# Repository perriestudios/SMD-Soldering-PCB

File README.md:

# EE201 - Computer Hardware Skills

## SMD Soldering Practice Board

This PCB was designed with the goal of teaching students how to solder surface mount components. 

### Logic
The core logic of the circuit is the logic gates NOT, AND, OR and XOR. There is a multiplexer the outputs of one of these gates to the LED used for indication.

### Inputs
Power supply for the PCB is through a Type-C USB.

There are two tactile switches (push buttons), used to emulate the inputs A and B for the logic gates. The circuit is in active-high configuration with a weak pull-down resistor of 1k. This value was chosen to consolidate the BOM and limit the number of unique resistors(since LEDs also need current limiting resistors).

A DIP Switch is used to set the MUX configuration of Enable, S0 and S1. The other two inputs of the DIP switch can be used as a back up for inputs A and B.

### More SMT Packages Section

This section is used to provide an overview of some commonly available SMD packages of Passives, Transistors and ICs. Students will not solder this, it is just to give them a feel of how big components are.

### Packages that Students will be Soldering

- Resistors: 0805 and 1206
- LED: 1206
- Logic Gates: SOT323
- MUX: SOIC16
- Capacitor - 0603
- Tactile Switches - 6mmx6mm
- DIP Switch - 2.54mm pitch

### Design Choices

In the process of completing this design, there were several tradeoffs and decisions made. The biggest factor influencing the choices was a circuit of reasonable complexity for Sophomores to solder in approximately 1 hour.

- Logic gates were chosen as the design as it would be intuitive and fun. Some of the other ideas considered were a Digital Dice, Digital Modulator(PPM, PWM, PAM), a device that would indicate a threshold (temperature, etc).
- Limited the number of components to 15
- Limited the package size to 0805

### Possible improvements

- Wanted to interface an RGB Led, but didn't proceed considering cost and complexity of soldering.
- Find a way to control the routing of inputs of the logic gates. Currently there is only routing over the outputs. The logic gates will be draining power unnecessarily.
- Instead of using an off the shelf IC, one of the gates could be replaced with an actual TTL implementation. NOT gate would be the easiest.

### Acknowledgement

This design was inspired by [Educational Logic Gates PCB](https://www.pcbway.com/project/shareproject/Educational_logic_gates_PCB.html)

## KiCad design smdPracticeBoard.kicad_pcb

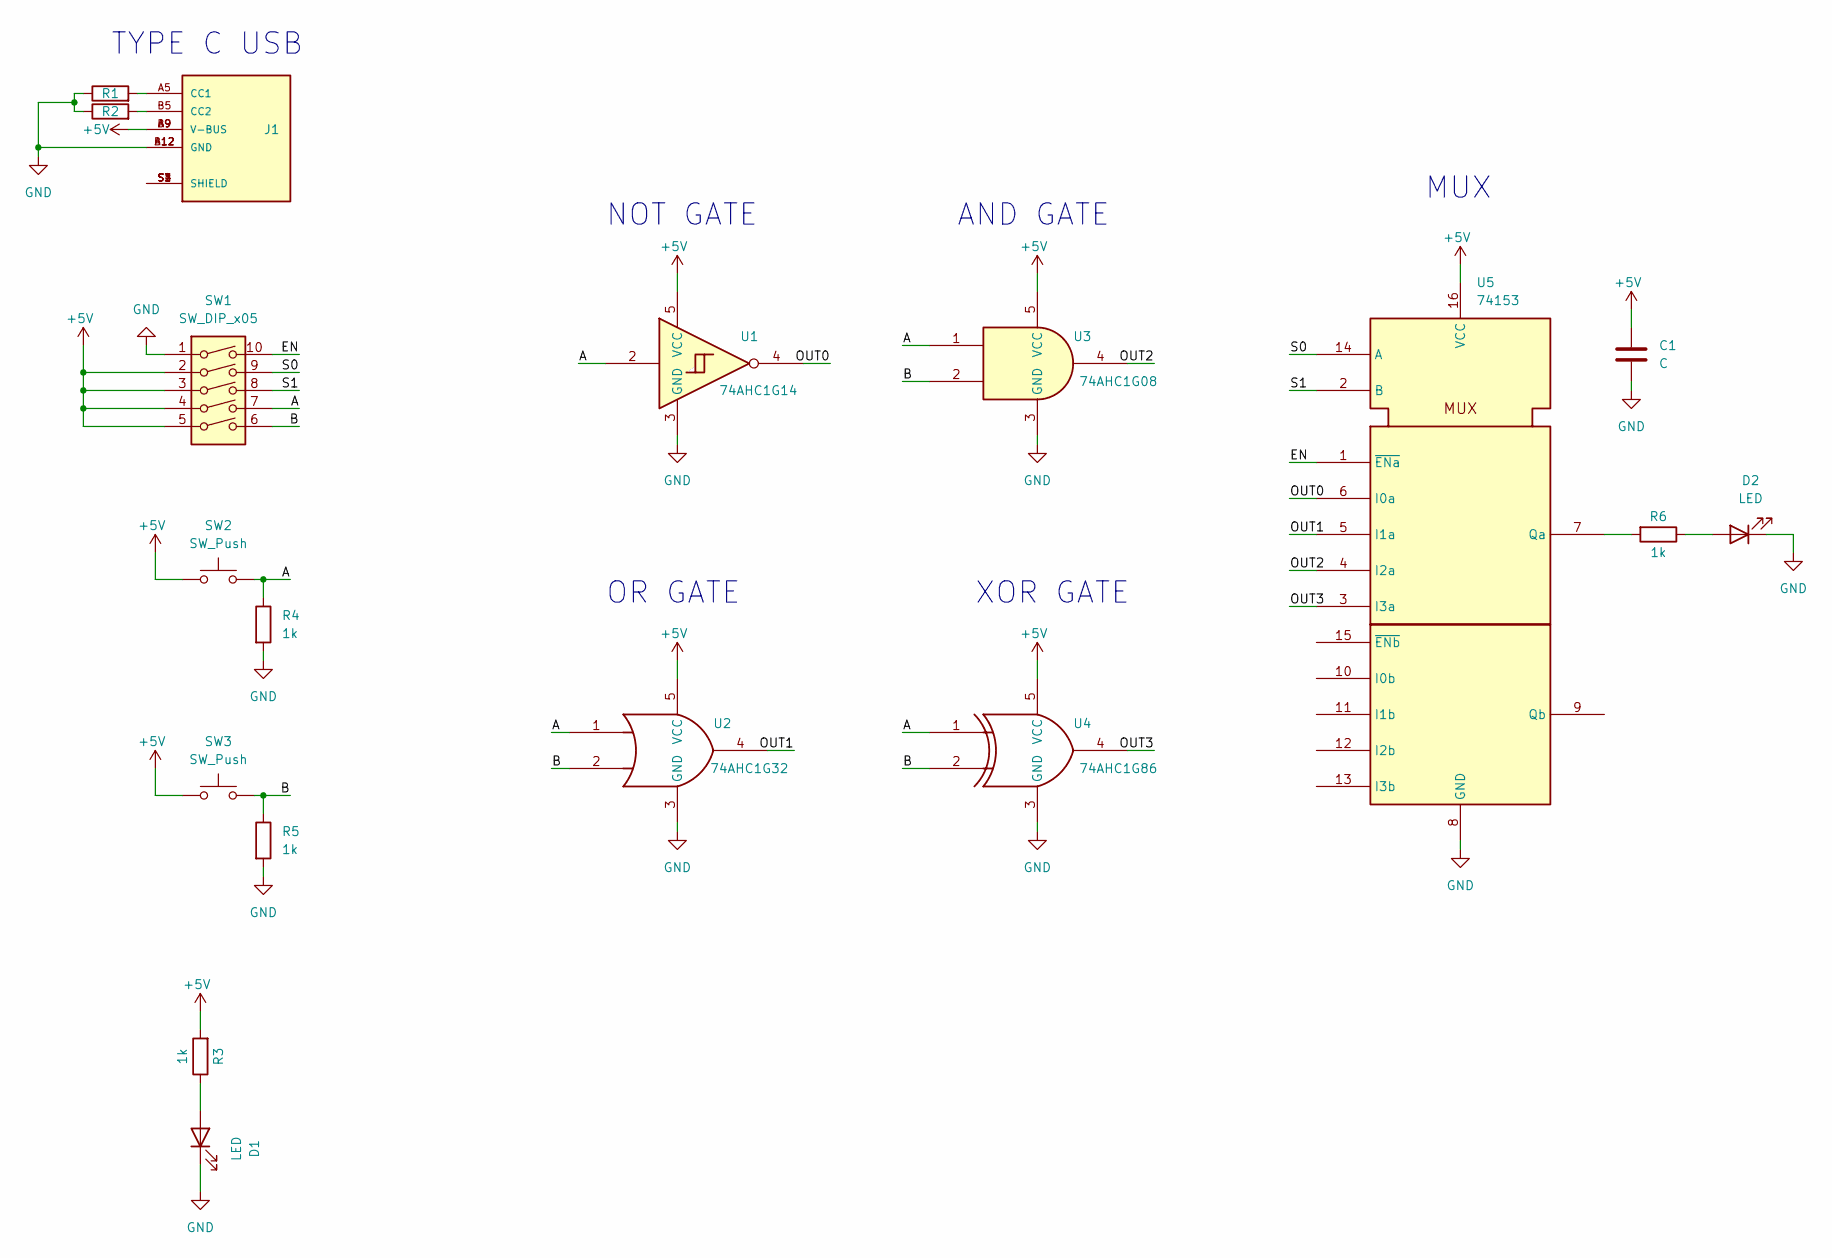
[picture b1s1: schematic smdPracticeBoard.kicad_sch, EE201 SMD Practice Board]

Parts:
C1: C; C_0603_1608Metric_Pad1.08x0.95mm_HandSolder
D1, D2: LED; LED_1206_3216Metric_Pad1.42x1.75mm_HandSolder
J1: UJC-HP-3-SMT-TR; CUI_UJC-HP-3-SMT-TR; PARTREV 04/30/2020
R1, R2: R; R_0805_2012Metric
R3, R4, R5, R6: 1k; R_1206_3216Metric_Pad1.30x1.75mm_HandSolder
SW1: SW_DIP_x05; CTS-219-5MST-0
SW2, SW3: SW_Push; SW_Push_1P1T_NO_6x6mm_H9.5mm
U1: 74AHC1G14; SOT-23-5_HandSoldering
U2: 74AHC1G32; SOT-23-5_HandSoldering
U3: 74AHC1G08; SOT-23-5_HandSoldering
U4: 74AHC1G86; SOT-23-5_HandSoldering
U5: 74153; SOIC-16_3.9x9.9mm_P1.27mm

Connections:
+5V: C1.1, J1.A9 (V-BUS), J1.B9 (V-BUS), R3.2, SW1.2, SW1.3, SW1.4, SW1.5, SW2.1, SW3.1, U1.5 (VCC), U2.5 (VCC), U3.5 (VCC), U4.5 (VCC), U5.16 (VCC)
/A: R4.1, SW1.7, SW2.2, U1.2, U2.1, U3.1, U4.1
/B: R5.1, SW1.6, SW3.2, U2.2, U3.2, U4.2
/EN: SW1.10, U5.1 (~ENa)
/OUT0: U1.4, U5.6 (I0a)
/OUT1: U2.4, U5.5 (I1a)
/OUT2: U3.4, U5.4 (I2a)
/OUT3: U4.4, U5.3 (I3a)
/S0: SW1.9, U5.14 (A)
/S1: SW1.8, U5.2 (B)
GND: C1.2, D1.1 (K), D2.1 (K), J1.A12 (GND), J1.B12 (GND), R1.1, R2.1, R4.2, R5.2, SW1.1, U1.3 (GND), U2.3 (GND), U3.3 (GND), U4.3 (GND), U5.8 (GND)
unnamed: D1.2 (A), R3.1
unnamed: D2.2 (A), R6.1
unnamed: J1.A5 (CC1), R1.2
unnamed: J1.B5 (CC2), R2.2
unnamed: J1.S1 (SHIELD), J1.S2 (SHIELD), J1.S3 (SHIELD), J1.S4 (SHIELD)
unnamed: R6.2, U5.7 (Qa)

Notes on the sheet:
NOT GATE
OR GATE
MUX
XOR GATE
TYPE C USB
AND GATE

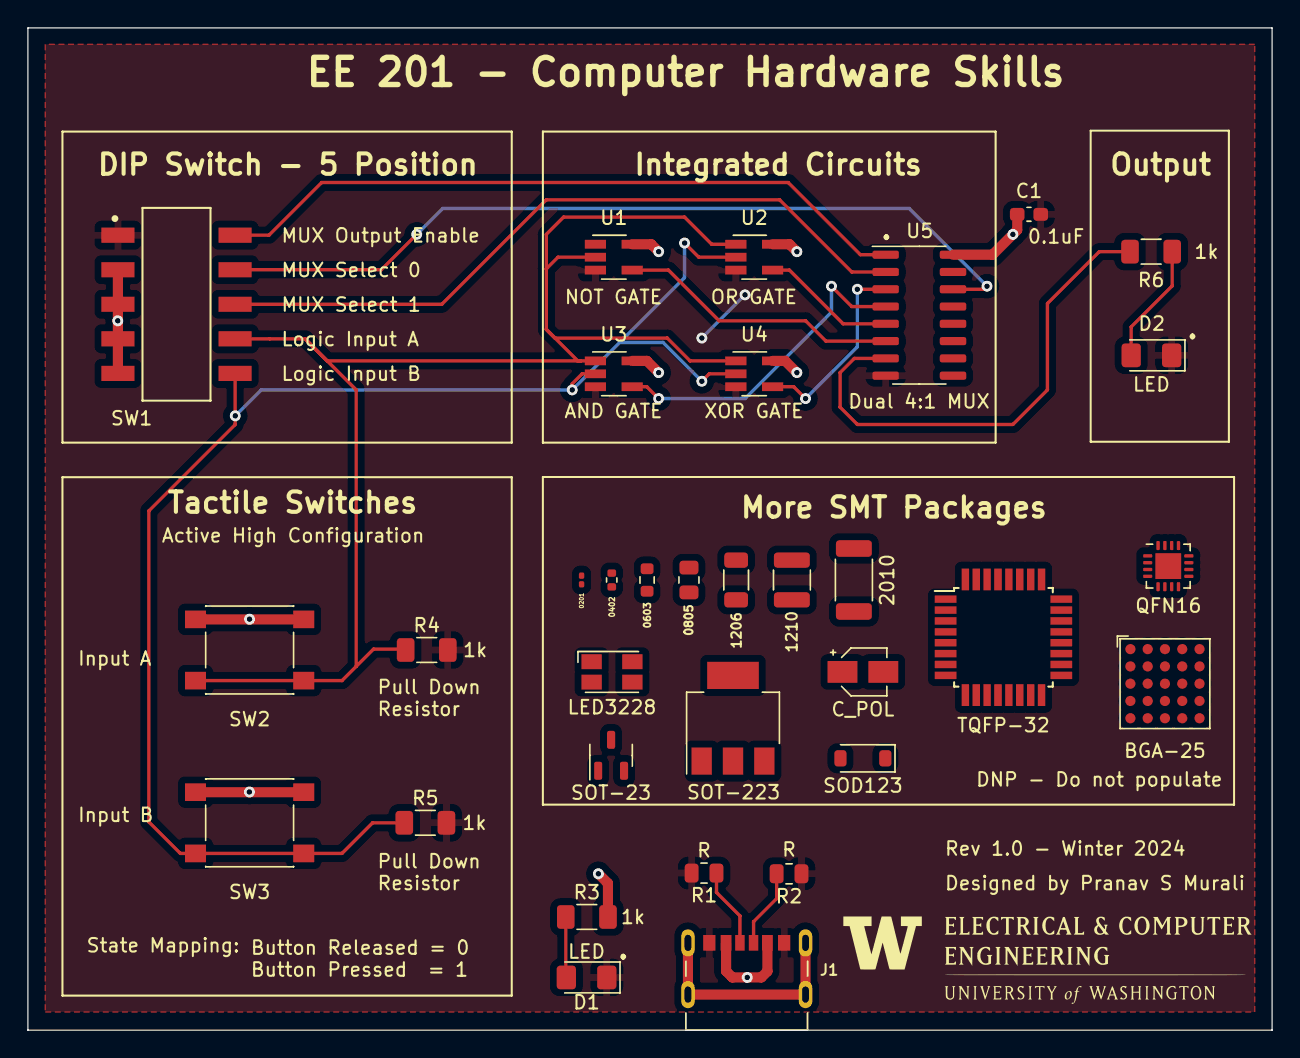
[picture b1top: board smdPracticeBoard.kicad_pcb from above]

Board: 2 copper layers, 91.4 x 73.7 mm, 31 parts (0 on the bottom side), 17 nets.

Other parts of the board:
0201: R_0201_0603Metric
0402: R_0402_1005Metric
0603: R_0603_1608Metric
0805: R_0805_2012Metric
1206: R_1206_3216Metric
1210: R_1210_3225Metric
2010: R_2010_5025Metric
BGA-25: BGA-25_6.35x6.35mm_Layout5x5_P1.27mm
C_POL: CP_Elec_3x5.3
LED3228: LED_Avago_PLCC4_3.2x2.8mm_CW
QFN16: QFN-16-1EP_3x3mm_P0.5mm_EP1.9x1.9mm
SOD123: D_SOD-123
TQFP-32: TQFP-32_7x7mm_P0.8mm

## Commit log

2024-01-08 Committing rev1 files
2024-01-08 Added documentation
